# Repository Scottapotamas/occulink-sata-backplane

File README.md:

# Occulink 4i to 4x SATA Backplane

A quad 2.5in SATA 'backplane' which connects via SFF-8611 (Occulink).

Intended as a one-off to increase packaging density (and neaten wiring) for my SFF flash-storage server.

# Data

This board aims to behave in the same manner as the Occulink CBL-SAST-0933 cable which uses a SFF-8611 connector to break out 4x SATA 7-pin connectors.

On the Asrock Rack X570D4I-2T motherboard I'm using, the OCU1 and OCU2 connectors are connected via the chipset and can operate in PCIe4x4 or 4x SATA mode.

# Power

In some situations (mine) the motherboard provides a power connector.

I don't include 3.3V supply to the disks, as most manufacturers don't use it, and some re-use the 3.3V pins for out-of-spec functionality (looking at you WD).

This board matches the pinout with the same Molex MicroFit 4-pin connector. It's also really easy to create a custom loom from a modular powersupply.

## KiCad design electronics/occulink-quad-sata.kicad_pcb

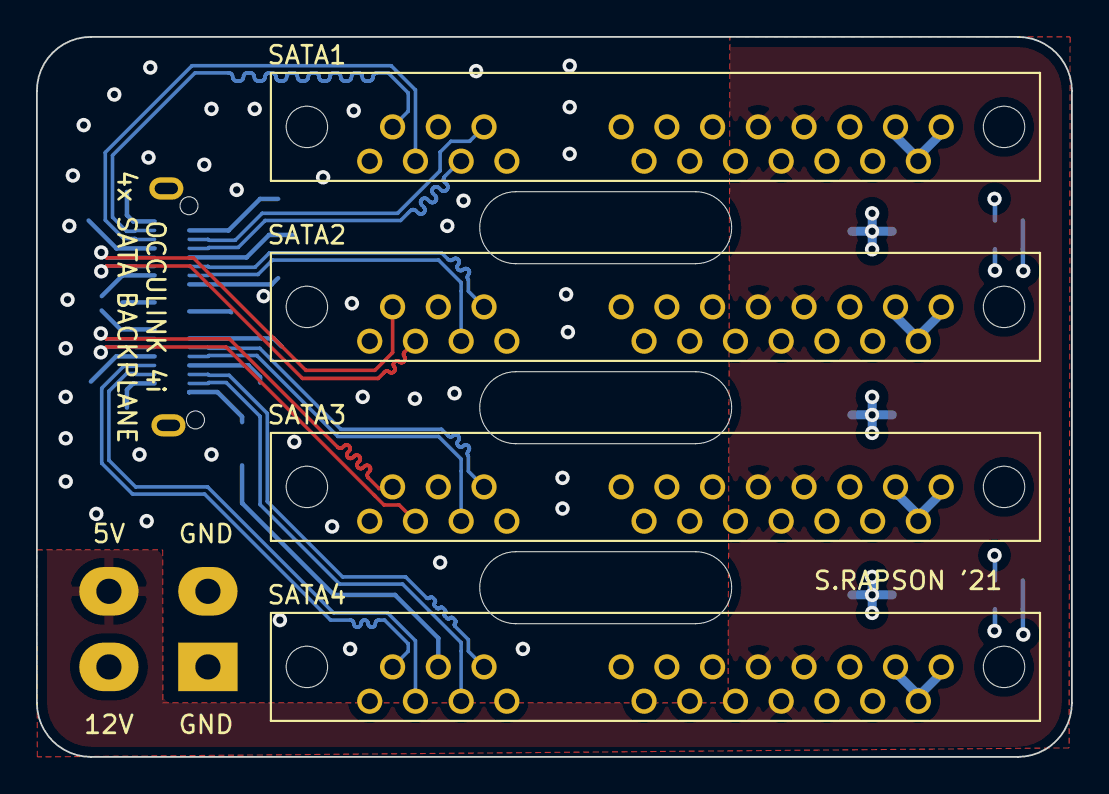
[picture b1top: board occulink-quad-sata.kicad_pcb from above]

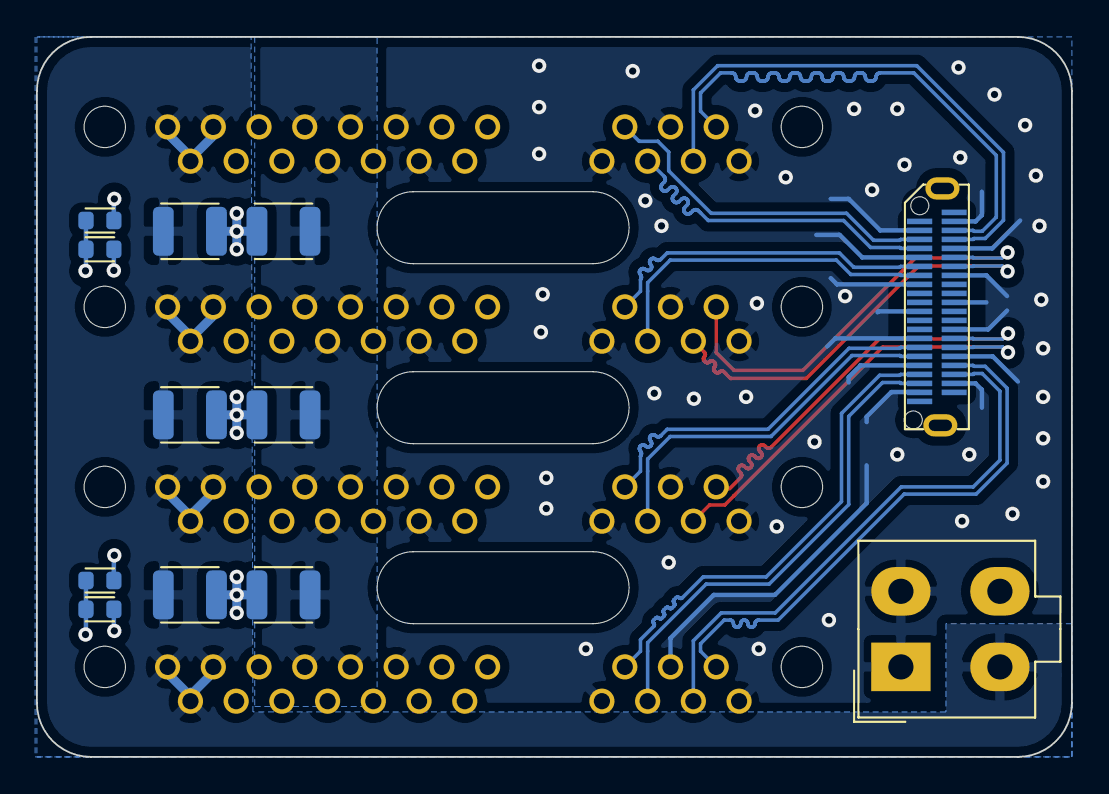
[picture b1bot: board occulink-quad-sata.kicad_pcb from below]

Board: 4 copper layers, 57.5 x 40.0 mm, 16 parts (12 on the bottom side), 23 nets.

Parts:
C1, C2, C3, C5, C6, C7: 10u_X7S_3225M; CAPC3225X170N
P0: MOLEX_NANOPITCH_42_WAY; MOLEX_NANOPITCH_171983-2342
P1, P2, P3, P4: MOLEX_SATA_COMBO; MOLEX_SATA_877011001
P5: MOLEX_MINIFIT_JR_2x2_WAY; Molex_Mini-Fit_Jr_5566-04A_2x02_P4.20mm_Vertical
R1, R2, R3, R4: 0R_1608M; RESC1608X50N

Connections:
+5V: C5.1, C6.1, C7.1, P1.P7, P1.P8, P1.P9, P2.P7, P2.P8, P2.P9, P3.P7, P3.P8, P3.P9, P4.P7, P4.P8, P4.P9, P5.4
+12V: C1.2, C2.2, C3.2, P1.P13, P1.P14, P1.P15, P2.P13, P2.P14, P2.P15, P3.P13, P3.P14, P3.P15, P4.P13, P4.P14, P4.P15, P5.3
/RX0+: P0.A3, P1.S6
/RX0-: P0.A4, P1.S5
/RX1+: P0.A6, P2.S6
/RX1-: P0.A7, P2.S5
/RX2+: P0.A15, P3.S6
/RX2-: P0.A16, P3.S5
/RX3+: P0.A18, P4.S6
/RX3-: P0.A19, P4.S5
/TX0+: P0.B3, P1.S2
/TX0-: P0.B4, P1.S3
/TX1+: P0.B6, P2.S2
/TX1-: P0.B7, P2.S3
/TX2+: P0.B15, P3.S2
/TX2-: P0.B16, P3.S3
/TX3+: P0.B18, P4.S2
/TX3-: P0.B19, P4.S3
GND: C1.1, C2.1, C3.1, C5.2, C6.2, C7.2, P0.A2, P0.A5, P0.A8, P0.A11, P0.A14, P0.A17, P0.A20, P0.B2, P0.B5, P0.B8, P0.B11, P0.B14, P0.B17, P0.B20, P1.P4, P1.P5, P1.P6, P1.P10, P1.P12, P1.S1, P1.S4, P1.S7, P2.P4, P2.P5, P2.P6, P2.P10, P2.P12, P2.S1, P2.S4, P2.S7, P3.P4, P3.P5, P3.P6, P3.P10, P3.P12, P3.S1, P3.S4, P3.S7, P4.P4, P4.P5, P4.P6, P4.P10, P4.P12, P4.S1, P4.S4, P4.S7, P5.1, P5.2, R1.2, R2.2, R3.2, R4.2
unnamed: P1.P11, R1.1
unnamed: P2.P11, R2.1
unnamed: P3.P11, R3.1
unnamed: P4.P11, R4.1

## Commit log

2021-04-30 Stubbed connectors onto sch/pcb
    Made symbols and footprints
2021-05-01 Continued schematic
2021-05-02 PCB layout tests
2021-05-02 Continued routing/layout
    Most pours done
2021-05-03 Diff pair skew tuning
2021-05-03 Add SFF-9402 spec to docs folder
    Describes occulink 4i pinout for SAS4 usage etc
2021-05-04 Minor board tweaks
2021-05-05 README updated, added renders and images of motherboard
